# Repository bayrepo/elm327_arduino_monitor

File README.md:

# elm327_arduino_monitor
Project for reading data by arduino from ELM237 via bluetooth and visualise data.

For building needed:

* Arduino IDE
* Installed Adafruit_GFX_Library
* Installed Adafruit_SSD1306
* Installed BluetoothHC05 - https://github.com/BayRepoOrg/Bluetooth_HC05
* Installed ELMDuino
* Installed U8g2_for_Adafruit_GFX
* Installed U8g2
* Installed GFX_Library_for_Arduino

Description of work https://brepo.ru/post/vizualizaciya-dannykh-schityvaemykh-s-elm327-adaptera-cherez-bluetooth-na-arduino

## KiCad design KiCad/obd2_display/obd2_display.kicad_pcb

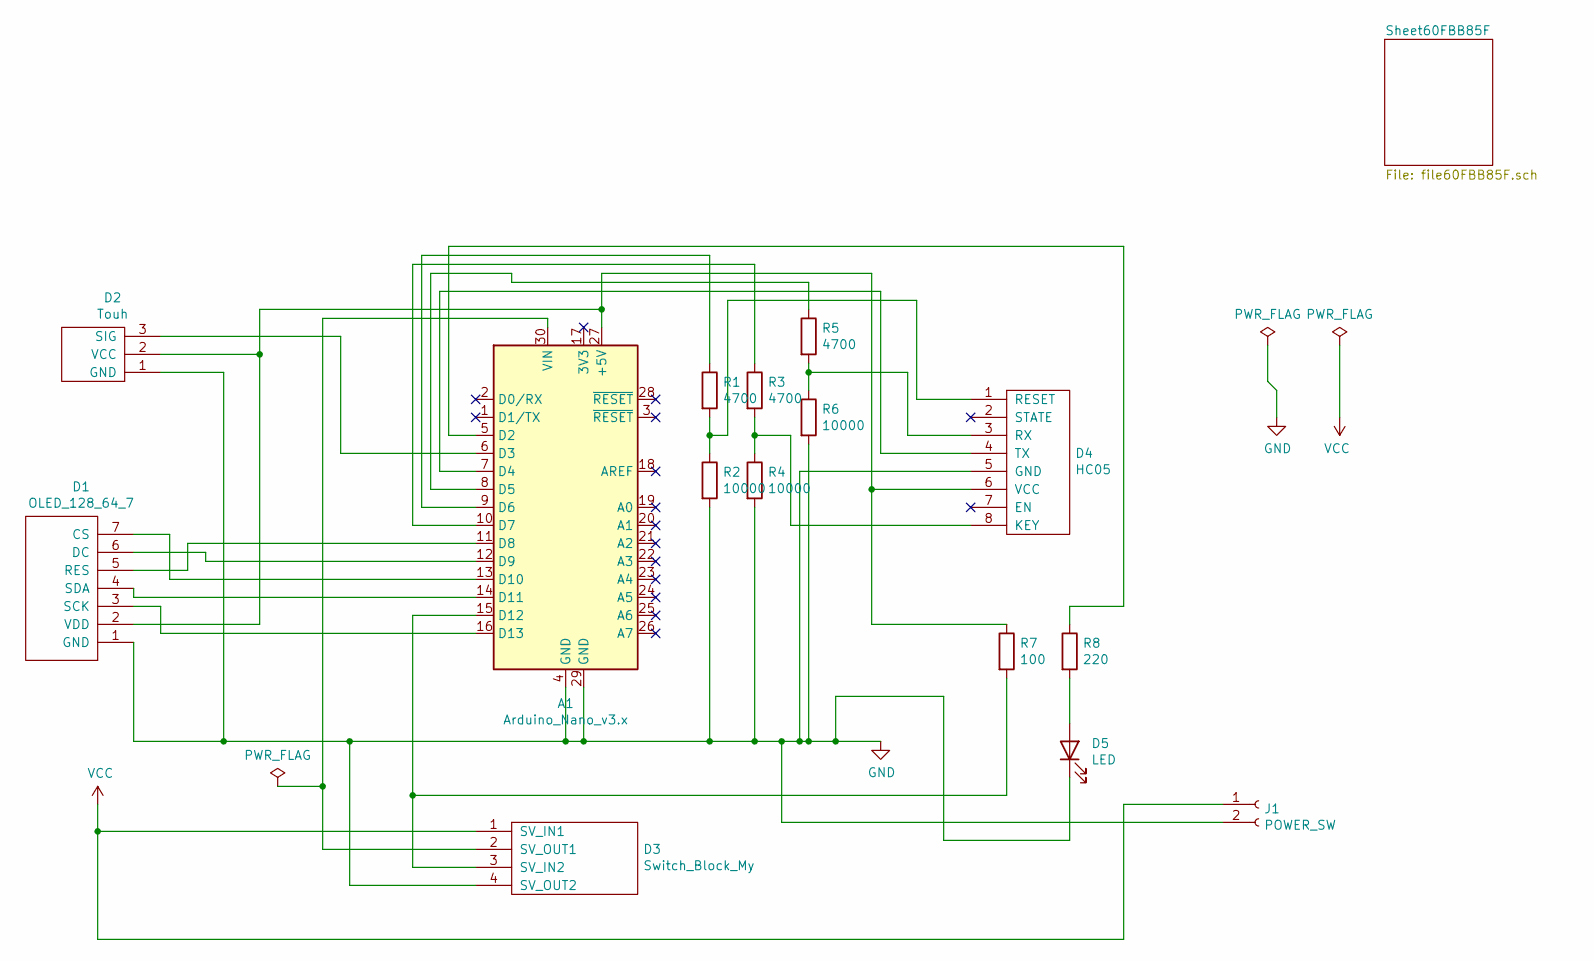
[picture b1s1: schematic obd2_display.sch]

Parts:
A1: Arduino_Nano_v3.x; DIP-30_590_ELL
D1: OLED_128_64_7; SIP-7
D2: Touh; SIP-3
D3: Switch_Block_My; SIP-4
D4: HC05; SIP-8
D5: LED; SIP-2
J1: POWER_SW; SIP-2
R1, R3, R5: 4700; R_Axial_DIN0204_L3.6mm_D1.6mm_P5.08mm_Horizontal
R2, R4, R6: 10000; R_Axial_DIN0204_L3.6mm_D1.6mm_P5.08mm_Horizontal
R7: 100; R_Axial_DIN0204_L3.6mm_D1.6mm_P5.08mm_Horizontal
R8: 220; R_Axial_DIN0204_L3.6mm_D1.6mm_P5.08mm_Horizontal

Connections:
GND: A1.4 (GND), A1.29 (GND), D1.1 (GND), D2.1 (GND), D3.4 (SV_OUT2), D4.5 (GND), D5.1 (K), J1.2, R2.2, R4.2, R6.2; also elsewhere on the board
unnamed: A1.5 (D2), R8.1
unnamed: A1.6 (D3), D2.3 (SIG)
unnamed: A1.7 (D4), D4.4 (TX)
unnamed: A1.8 (D5), R5.1
unnamed: A1.9 (D6), R1.1
unnamed: A1.10 (D7), R3.1
unnamed: A1.11 (D8), D1.5 (RES)
unnamed: A1.12 (D9), D1.6 (DC)
unnamed: A1.13 (D10), D1.7 (CS)
unnamed: A1.14 (D11), D1.4 (SDA)
unnamed: A1.15 (D12), D3.3 (SV_IN2), R7.2
unnamed: A1.16 (D13), D1.3 (SCK)
unnamed: A1.27 (+5V), D1.2 (VDD), D2.2 (VCC), D4.6 (VCC), R7.1
unnamed: A1.30 (VIN), D3.2 (SV_OUT1)
unnamed: D4.1 (RESET), R1.2, R2.1
unnamed: D4.3 (RX), R5.2, R6.1
unnamed: D4.8 (KEY), R3.2, R4.1
unnamed: D5.2 (A), R8.2
VCC: D3.1 (SV_IN1), J1.1; also elsewhere on the board

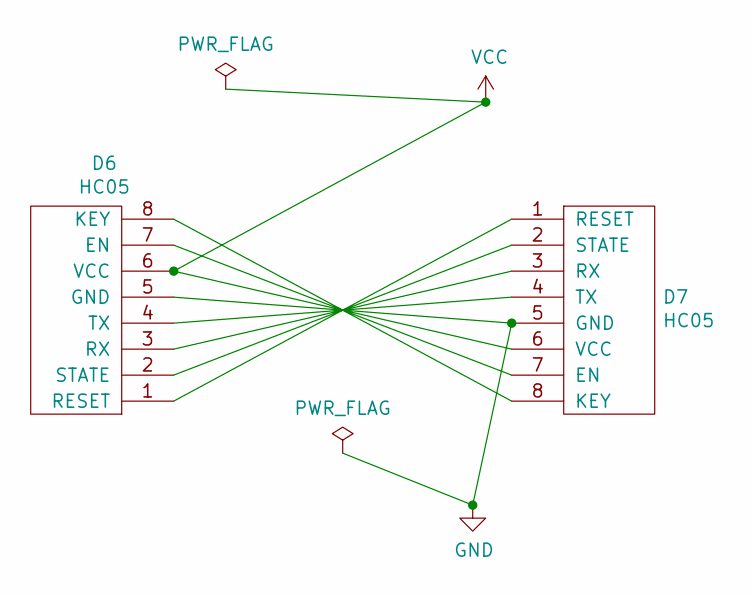
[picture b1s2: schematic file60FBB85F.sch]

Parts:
D6, D7: HC05; SIP-8

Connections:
GND: D6.5 (GND), D7.5 (GND); also elsewhere on the board
unnamed: D6.1 (RESET), D7.1 (RESET)
unnamed: D6.2 (STATE), D7.2 (STATE)
unnamed: D6.3 (RX), D7.3 (RX)
unnamed: D6.4 (TX), D7.4 (TX)
unnamed: D6.7 (EN), D7.7 (EN)
unnamed: D6.8 (KEY), D7.8 (KEY)
VCC: D6.6 (VCC), D7.6 (VCC); also elsewhere on the board

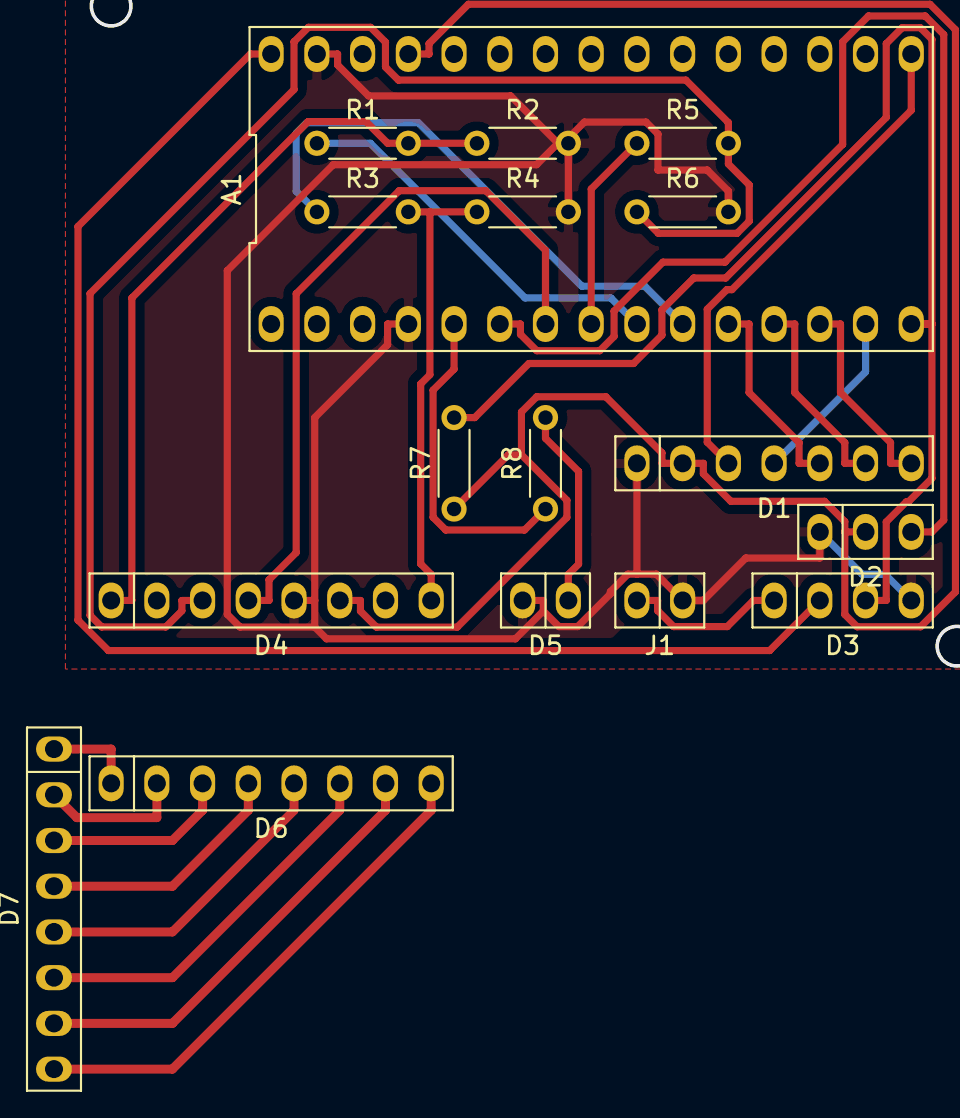
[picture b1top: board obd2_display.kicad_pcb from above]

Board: 2 copper layers, 17 parts (0 on the bottom side), 26 nets.

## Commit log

2021-07-13 Add sourcew
2021-08-12 Added KiCad, STL and WDT
2022-03-09 Fix ELMDuino updates. Use get_response instead of status
